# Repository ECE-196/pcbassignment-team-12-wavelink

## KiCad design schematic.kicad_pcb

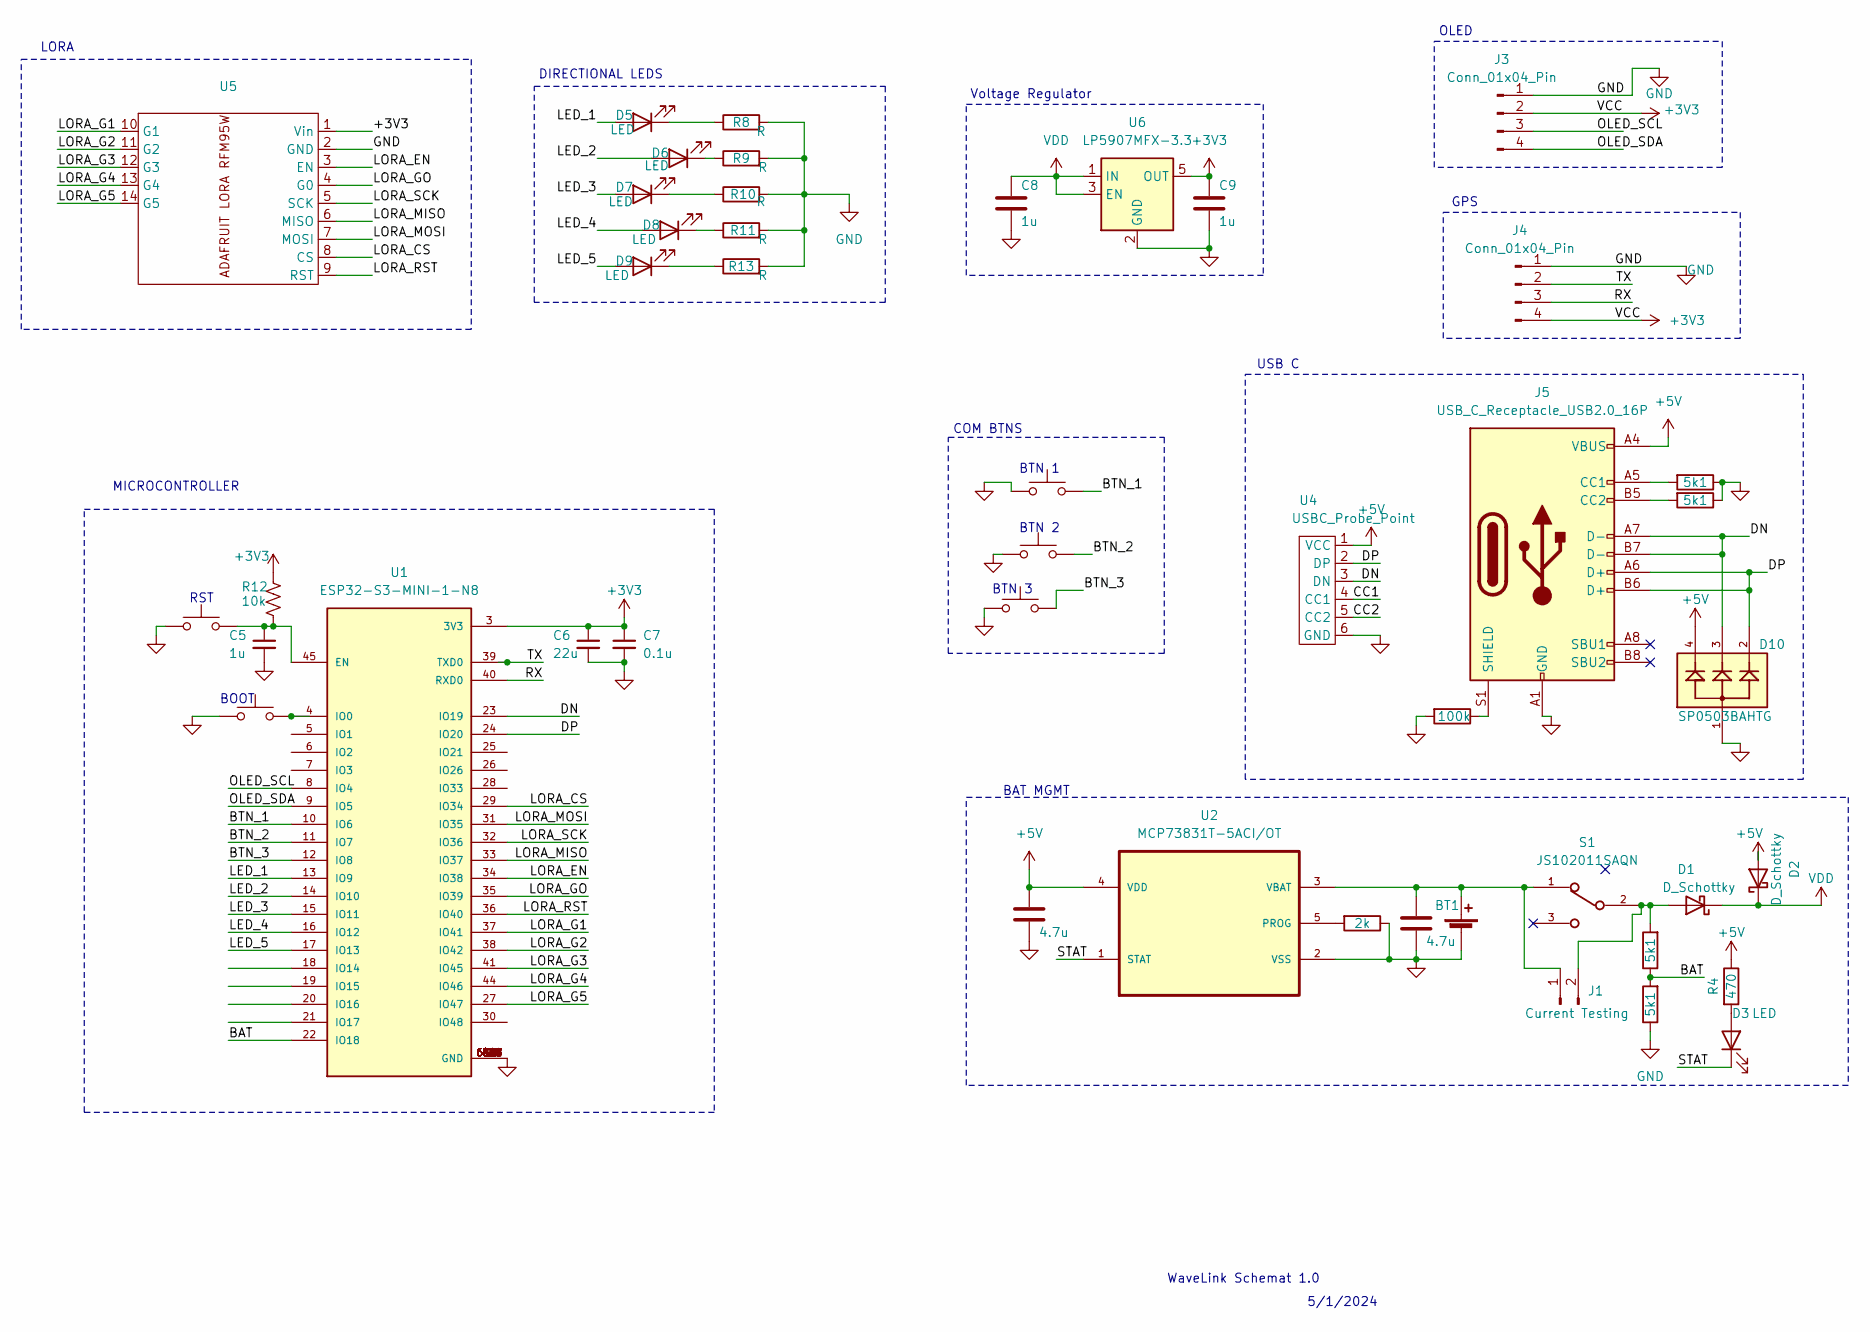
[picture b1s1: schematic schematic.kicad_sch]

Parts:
BT1: 3.7; PinSocket_1x02_P2.54mm_Vertical
C1, C2: 4.7u; C_0805_2012Metric
C5, C8, C9: 1u; C_0805_2012Metric
C6: 22u; C_0805_2012Metric
C7: 0.1u; C_0805_2012Metric
D1, D2: D_Schottky; D_SOD-523
D3, D5, D6, D7, D8, D9: LED; LED_0805_2012Metric
D10: SP0503BAHTG; SOT-143; PARTREV N/A
J1: Current Testing; PinHeader_1x02_P1.00mm_Vertical
J3, J4: Conn_01x04_Pin; PinHeader_1x04_P2.54mm_Vertical
J5: USB_C_Receptacle_USB2.0_16P; USB_C_Receptacle_GCT_USB4105-xx-A_16P_TopMnt_Horizontal
R1: 2k; R_0805_2012Metric
R2, R3, R5, R6: 5k1; R_0805_2012Metric
R4: 470; R_0805_2012Metric
R7: 100k; R_0805_2012Metric
R8, R9, R10, R11, R13: R; R_0805_2012Metric
R12: 10k; R_0805_2012Metric
S1: JS102011SAQN; SW_SPDT_CK_JS102011SAQN
SW1, SW3, SW4, SW5, SW6: Boot; SW_Push_1P1T_NO_Vertical_Wuerth_434133025816
U1: ESP32-S3-MINI-1-N8; XCVR_ESP32-S3-MINI-1-N8; PARTREV v0.6
U2: MCP73831T-5ACI/OT; SOT-23-5; MPN MCP73831T-5ACI/OT
U4: USBC_Probe_Point; PinHeader_1x06_P1.00mm_Vertical
U5: Lora_Adafruit
U6: LP5907MFX-3.3; SOT-23-5

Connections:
+3V3: C6.1, C7.1, C9.1, J3.2, J4.4, R12.1, U1.3 (3V3), U5.1 (Vin), U6.5 (OUT)
+5V: C1.1, D2.2 (A), D10.4, J5.A4 (VBUS), J5.A9 (VBUS), J5.B4 (VBUS), J5.B9 (VBUS), R4.1, U2.4 (VDD), U4.1 (VCC)
/BAT: R2.1, R3.2, U1.22 (IO18)
/BTN_1: SW4.2, U1.10 (IO6)
/BTN_2: SW5.2, U1.11 (IO7)
/BTN_3: SW6.2, U1.12 (IO8)
/CC1: U4.4 (CC1)
/CC2: U4.5 (CC2)
/DN: D10.3, J5.A7 (D-), J5.B7 (D-), U1.23 (IO19), U4.3 (DN)
/DP: D10.2, J5.A6 (D+), J5.B6 (D+), U1.24 (IO20), U4.2 (DP)
/LED_1: D5.2 (A), U1.13 (IO9)
/LED_2: D6.2 (A), U1.14 (IO10)
/LED_3: D7.2 (A), U1.15 (IO11)
/LED_4: D8.2 (A), U1.16 (IO12)
/LED_5: D9.2 (A), U1.17 (IO13)
/LORA_CS: U1.29 (IO34), U5.8 (CS)
/LORA_EN: U1.34 (IO38), U5.3 (EN)
/LORA_G1: U1.37 (IO41), U5.10 (G1)
/LORA_G2: U1.38 (IO42), U5.11 (G2)
/LORA_G3: U1.41 (IO45), U5.12 (G3)
/LORA_G4: U1.44 (IO46), U5.13 (G4)
/LORA_G5: U1.27 (IO47), U5.14 (G5)
/LORA_GO: U1.35 (IO39), U5.4 (G0)
/LORA_MISO: U1.33 (IO37), U5.6 (MISO)
/LORA_MOSI: U1.31 (IO35), U5.7 (MOSI)
/LORA_RST: U1.36 (IO40), U5.9 (RST)
/LORA_SCK: U1.32 (IO36), U5.5 (SCK)
/OLED_SCL: J3.3, U1.8 (IO4)
/OLED_SDA: J3.4, U1.9 (IO5)
/RX: J4.3, U1.40 (RXD0)
/STAT: D3.1 (K), U2.1 (STAT)
/TX: J4.2, U1.39 (TXD0)
GND: BT1.2 (-), C1.2, C2.2, C5.2, C6.2, C7.2, C8.2, C9.2, D10.1, J3.1, J4.1, J5.A1 (GND), J5.A12 (GND), J5.B1 (GND), J5.B12 (GND), R1.1, R3.1, R5.1, R6.1, R7.2, R8.2, R9.2, R10.2, R11.2, R13.2, SW1.1, SW3.1, SW4.1, SW5.1, SW6.1, U1.1 (GND), U1.2 (GND), U1.42 (GND), U1.43 (GND), U1.46 (GND), U1.47 (GND), U1.48 (GND), U1.49 (GND), U1.50 (GND), U1.51 (GND), U1.52 (GND), U1.53 (GND), U1.54 (GND), U1.55 (GND), U1.56 (GND), U1.57 (GND), U1.58 (GND), U1.59 (GND), U1.60 (GND), U1.61 (GND), U1.61_1 (GND), U1.61_2 (GND), U1.61_3 (GND), U1.61_4 (GND), U1.61_5 (GND), U1.61_6 (GND), U1.61_7 (GND), U1.61_8 (GND), U1.62 (GND), U1.63 (GND), U1.64 (GND), U1.65 (GND), U2.2 (VSS), U4.6 (GND), U5.2 (GND), U6.2 (GND)
unnamed: BT1.1 (+), C2.1, J1.1, S1.1, U2.3 (VBAT)
unnamed: D1.2 (A), J1.2, R2.2, S1.2
unnamed: D3.2 (A), R4.2
unnamed: D5.1 (K), R8.1
unnamed: D6.1 (K), R9.1
unnamed: D7.1 (K), R10.1
unnamed: D8.1 (K), R11.1
unnamed: D9.1 (K), R13.1
unnamed: J5.A5 (CC1), R6.2
unnamed: J5.B5 (CC2), R5.2
unnamed: J5.S1 (SHIELD), R7.1
unnamed: C5.1, R12.2, SW1.2, U1.45 (EN)
unnamed: SW3.2, U1.4 (IO0)
unnamed: R1.2, U2.5 (PROG)
VDD: C8.1, D1.1 (K), D2.1 (K), U6.1 (IN), U6.3 (EN)

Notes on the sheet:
GPS
OLED
RST
COM BTNS
USB C
BTN 2
BOOT
WaveLink Schemat 1.0
BAT MGMT
5/1/2024
Voltage Regulator
LORA
BTN 3
BTN 1
MICROCONTROLLER
DIRECTIONAL LEDS

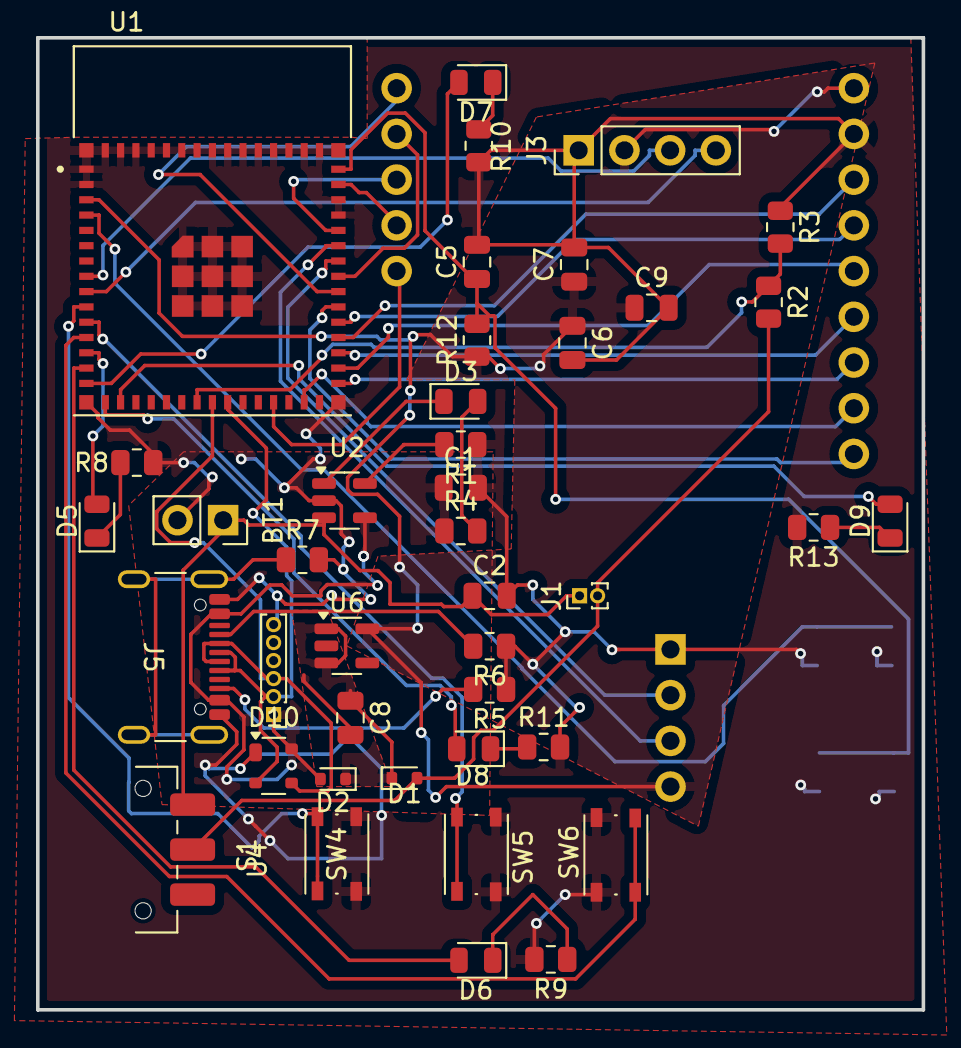
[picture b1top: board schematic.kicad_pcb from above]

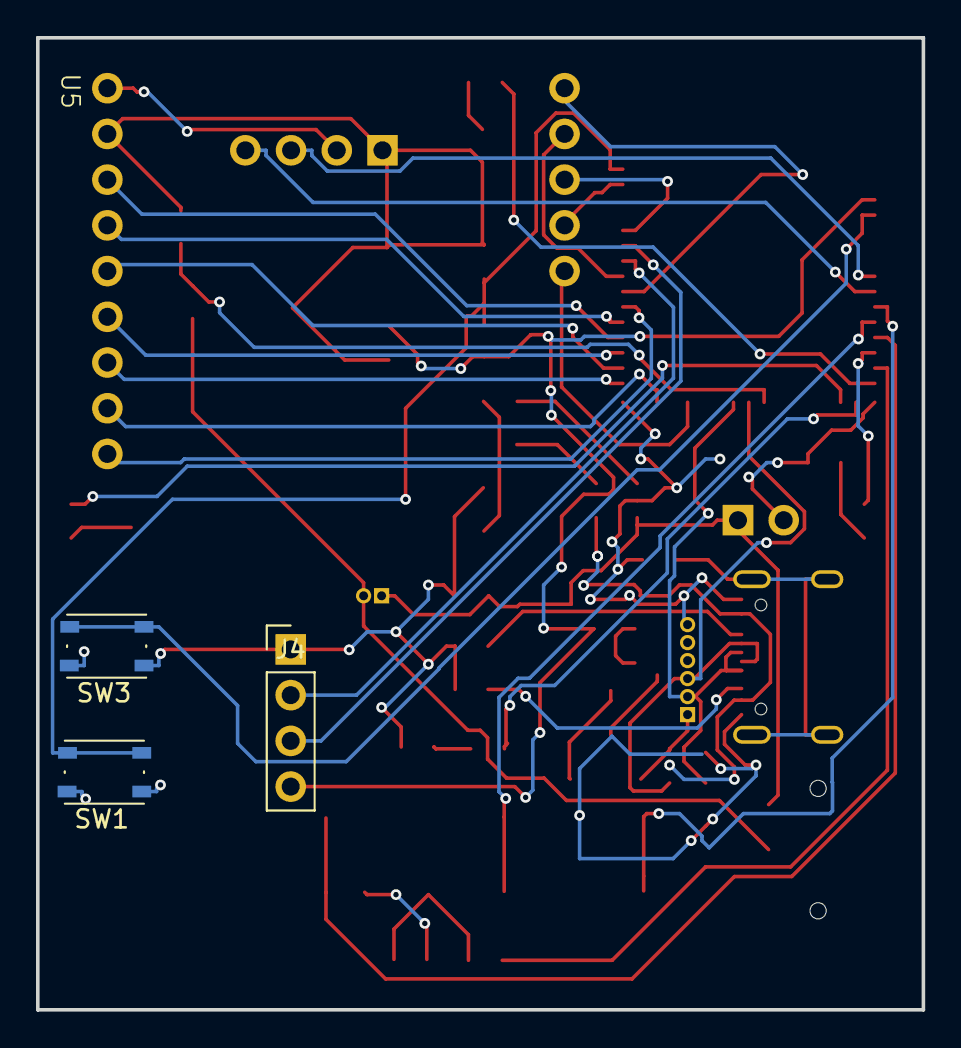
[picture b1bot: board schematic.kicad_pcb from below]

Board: 2 copper layers, 49.2 x 54.0 mm, 45 parts (4 on the bottom side), 46 nets.

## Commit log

2024-04-29 add deadline
2024-04-29 added schematic file
2024-04-29 image of the schematic
2024-04-30 updated image of schematic
2024-05-04 uploaded Schematic / PCB / any other needed files
2024-05-04 updated schematic image
2024-05-04 generate gerbers...
